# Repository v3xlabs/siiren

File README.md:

# SIIREN

An open-hardware digital notifier with ePaper display, esp32-s3, and removable battery.

> [!NOTE]
> This is a work in progress.

## Technical Specs

- **Processor**: esp32-s3
- **Inputs**
  - 5-btn slim d-pad
- **Outputs**:
  - ePaper display (specifics undecided)
- **Connectivity**:
  - USB-C (Power, Data & Flash)
  - Wifi & BLE

## Photos

See the [docs](docs) folder for the rendered schematics, PCBs, and 3D renders.

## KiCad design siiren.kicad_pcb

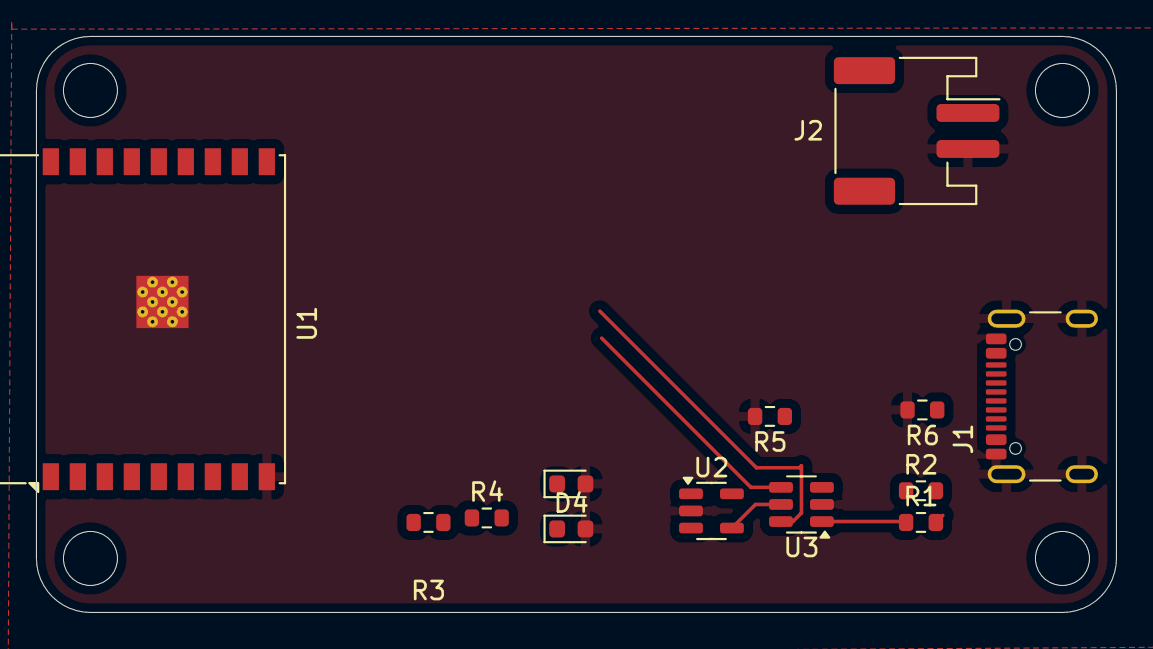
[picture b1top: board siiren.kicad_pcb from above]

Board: 2 copper layers, 60.0 x 32.0 mm, 14 parts (1 on the bottom side), 14 nets.

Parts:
D1, D4: D_Zener; D_0603_1608Metric
J1: USB_C_Receptacle_USB2.0_16P; USB_C_Receptacle_GCT_USB4105-xx-A_16P_TopMnt_Horizontal
J2: S2B-PH-SM4-TB(LF)(SN); JST_PH_S2B-PH-SM4-TB_1x02-1MP_P2.00mm_Horizontal
R1, R2: 22R; R_0603_1608Metric
R3: 200k; R_0603_1608Metric
R4: R; R_0603_1608Metric
R5, R6: 5k1; R_0603_1608Metric
SW2: K1-1210UN-01
U1: ESP32-C3-WROOM-02
U2: MCP73832-2-OT; SOT-23-5
U3: USBLC6-2SC6; SOT-23-6

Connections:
+3.3V: R4.2, U1.1 (3V3)
+BATT: J2.1, U2.3 (V_{BAT})
/MCU/ENABLE: R4.1, U1.2 (EN)
/MCU/USB_D+: U1.14 (IO19), U3.6 (I/O1)
/MCU/USB_D-: U1.13 (IO18), U3.4 (I/O2)
/USB/CC1: J1.A5 (CC1), R5.1
/USB/CC2: J1.B5 (CC2), R6.1
/USB/USB_D+_RAW: J1.A6 (D+), J1.B6 (D+), R1.2
/USB/USB_D-_RAW: J1.A7 (D-), J1.B7 (D-), R2.2
/USB/USB_DN: R2.1, U3.3 (I/O2)
/USB/USB_DP: R1.1, U3.1 (I/O1)
/USB/VBUS_DETECT: D4.1 (K), R3.1
GND: D1.2 (A), D4.2 (A), J1.A1 (GND), J1.A12 (GND), J1.B1 (GND), J1.B12 (GND), J1.S1 (SHIELD), J2.2, R5.2, R6.2, SW2.1 (A1), SW2.3 (B2), SW2.5 (D1), SW2.7 (E1), SW2.9 (C2), U1.9 (GND), U1.19 (GND), U2.2 (V_{SS}), U3.2 (GND)
VBUS: D1.1 (K), J1.A4 (VBUS), J1.A9 (VBUS), J1.B4 (VBUS), J1.B9 (VBUS), R3.2, U2.4 (V_{DD}), U3.5 (VBUS)

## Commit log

2025-07-11 Introduce gitignore
2025-07-11 Update schematic
2025-07-11 Update project
2025-07-11 Update backups
2025-07-11 Bump commit
2025-07-11 Introduce image generation
2025-07-11 Update project layout
2025-07-11 Update board color
2025-07-11 Update inputs
2025-07-11 Update render quality
2025-07-18 Update image rendering & relayout pcb
2025-07-18 Update image rendering
